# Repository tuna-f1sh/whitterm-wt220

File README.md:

```bash
        __        _______    ____  ____   ___
        \ \      / /_   _|  |___ \|___ \ / _ \
         \ \ /\ / /  | |_____ __) | __) | | | |
          \ V  V /   | |_____/ __/ / __/| |_| |
           \_/\_/    |_|    |_____|_____|\___/
       --- JBR Engineering Research Ltd 2019 ---
```

Design files, firmware and linux scripts for my _clever_ serial terminal, the
Whitterm-220 - WT-220. 

The WT-220 is a homage to the VT-220, providing a physical RS232 terminal with
the full features of a Linux computer running on a Raspberry Pi.

## Raspberry Pi Hat (./whitterm-hat)

KiCad design files for the rear io-panel:

* USB-C input for USB-PD high current (3 A) supply to RPi. LEDs indicate
  detected current profile from UFP. I2C lines made available to SAMD for
  playing with USB-C device modes.
* MAX3232 RS232 transceiver provides RS232 level interface to RPi UART and SAMD
  UART.
* SAMD21 microcontroller provides boot button control of RPi over I2C and
  buffered IO. Can be programmed over USB-C CDC-serial device or ISP.
* Control of RPi power supply from SAMD. Off by default allows safe start up, only when power input suitable/ready.
* DIP switch control of device UART connections (SAMD, RPi, RS232).
* Board replaces laser cut acrylic back piece from original design - it is
  both electronically and mechanically integrated.
* Lots of status LEDs 😃.

**There where a few green wires required for the first production (1.0). I
rolled these changes into the schematic but not fully updated the PCB.**

## Firmware (./firmware)

Arduino compatible firmware for rear panel SAMD21. Acts as I2C slave and
controls supply to RPi via 'Boot' button:

### Simplified State Diagram

```mermaid
graph TB;
    OFF-->|boot pressed 500 ms|ON;
    ON-->|I2C booted cmd recieved|BOOTED;
    ON-->|I2C recieve booted timeout 20000 ms|I2C_TIMEOUT;
    BOOTED-->|I2C recieve booted timeout 20000 ms|I2C_TIMEOUT;
    BOOTED-->|boot pressed 3000 ms|SHUTDOWN_REQUESTED;
    I2C_TIMEOUT-->|boot pressed 3000 ms|SHUTDOWN;
    I2C_TIMEOUT-->|I2C booted cmd recieved|BOOTED;
    SHUTDOWN_REQUESTED-->|I2C shutdown cmd|SHUTDOWN;
    SHUTDOWN_REQUESTED-->|boot pressed|ON;
    SHUTDOWN-->OFF;
```

## RPi Files (./rpi)

I started from a base Raspbian Lite image rather than Arch for this build.
Raspbian Lite is nice because I could install only what I wanted/needed. I
opted for I3WM since it's a keyboard terminal.

### Services

* boot: Runs shell script that displays boot ascii logo.
* i2c: Runs python I2C script (wt220-i2c.py) that configures case LEDs to act
  on RX/TX and then maintains link with I2C link with SAMD. Polls shutdown
  request state and acts on request by issuing system shutdown.
* poweroff: Runs on 'shutdown.target' and issues the final I2C shutdown
  command so that SAMD disables RPi 5 V.

### Config Files

Would make an install script for this if I was making more...

* xinitrc -> /etc/X11/xinit/xinitrc
* config.txt, cmdline.txt -> /boot/
* Xresources -> ~/.Xresources
* motd -> /etc/motd
* wt220-sshbanner.net -> /etc/wt220-sshbanner.net `Banner /etc/wt220-sshbanner.net` in
  /etc/ssh/sshd_config
* \*services. -> /lib/systemd/system/
* scripts -> /opt/wt220/

### Packages

Need to manually install
[`cool-retro-term`](https://github.com/Swordfish90/cool-retro-term)

Other packages in 'rpi/dpkg-selections.txt'

## Breakout (./whitterm-breakout)

DB9 GPIO breakout from V 1.0 rear panel

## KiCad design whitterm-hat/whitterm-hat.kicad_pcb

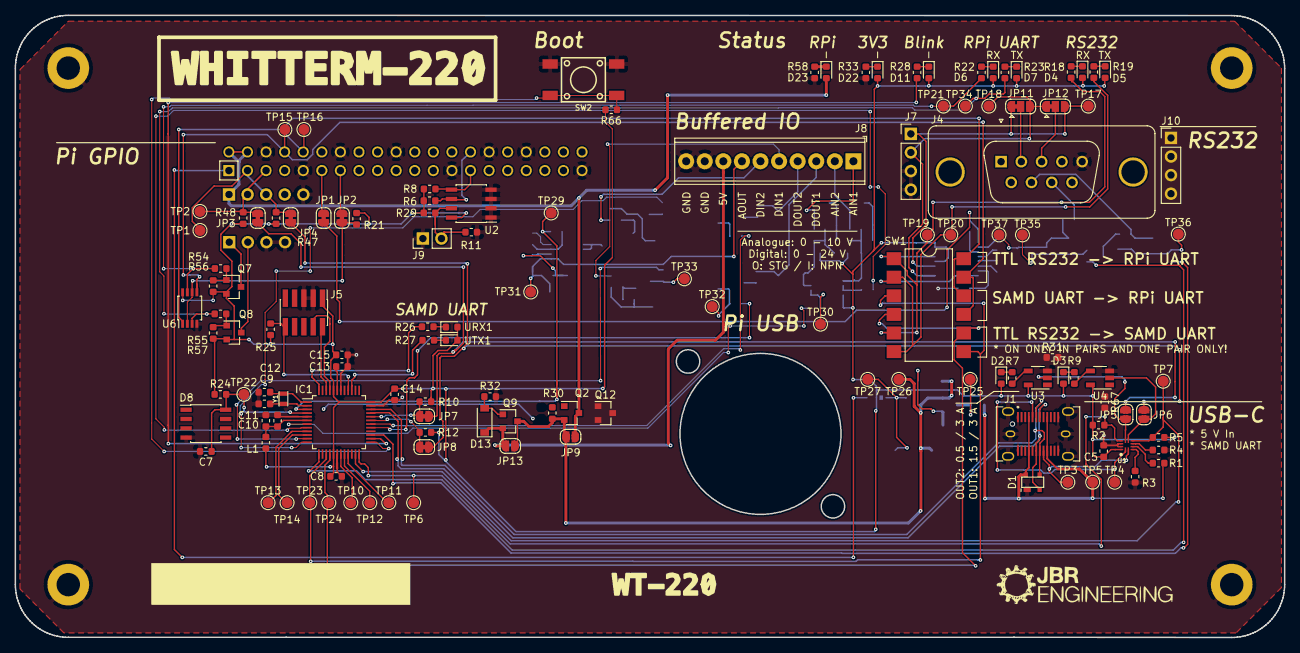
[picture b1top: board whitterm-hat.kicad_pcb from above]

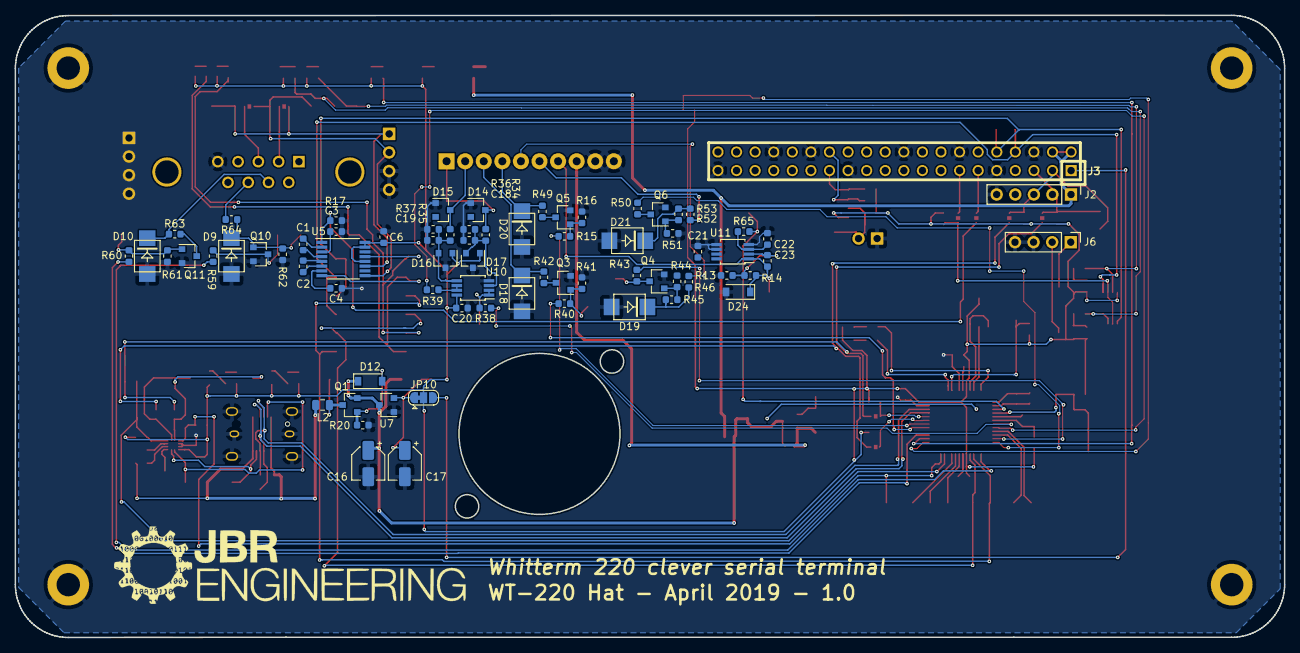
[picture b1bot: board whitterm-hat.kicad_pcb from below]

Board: 2 copper layers, 173.5 x 85.0 mm, 202 parts (72 on the bottom side), 127 nets.

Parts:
C1: 47nF; C_0603_1608Metric
C2, C3, C4: 330nF; C_0603_1608Metric
C5, C6, C18, C19, C20, C21: 100nF; C_0603_1608Metric
C7: 1uF; C_0603_1608Metric
C8, C10, C13, C14, C15: 0.1uF; C_0603_1608Metric
C9, C12: 15pF; C_0603_1608Metric
C11: 0.01uF; C_0603_1608Metric
C16, C17: 10uF; CP_Elec_4x5.3
C22: 470pF; C_0603_1608Metric
C23: 10pF; C_0603_1608Metric
D1: PRTR5V0U2X; SOT143B
D2: OUT2; LED_0603_1608Metric
D3: OUT1; LED_0603_1608Metric
D4: TLRX; LED_0603_1608Metric
D5: TLTX; LED_0603_1608Metric
D6: RXD; LED_0603_1608Metric
D7: TXD; LED_0603_1608Metric
D8: LM285D-2.5G; SOIC-8_3.9x4.9mm_P1.27mm
D9, D10, D18, D19, D20, D21: SMAJ30A-TR; D_DO-214AA
D11: D13; LED_0603_1608Metric
D12, D13: MMSZ16T1G; D_SOD-123
D14, D15: BZX84C10LT1G; D_SOT-23_ANK
D16, D17: BAV99; SOT-23
D22, D23: KP-2012MGC; LED_0603_1608Metric
D24: SMAJ12A-TR; D_SOD-123
IC1: SAMD21G18A; TQFP-48_7x7mm_P0.5mm
J1: USB_C_Receptacle; USB_C_Receptacle_JAE_DX07S024WJ1R350
J2: Touch I2C; PinHeader_1x05_P2.54mm_Vertical
J3: 40HAT; HEADER-2x20-REVERSE
J4: DB9_Male; DSUB-9_Male_Vertical_P2.77x2.84mm_MountingHoles
J5: Conn_02x05_Odd_Even; PinHeader_2x05_P1.27mm_Vertical_SMD
J6, J7, J10: Conn_01x04_Female; PinHeader_1x04_P2.54mm_Vertical
J8: Conn_01x10_Female; TerminalBlock_Phoenix_MPT-0,5-10-2.54_1x10_P2.54mm_Horizont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
J9: CONN_01X02; PinHeader_1x02_P2.54mm_Vertical
JP1, JP2, JP3, JP4, JP7, JP8: Jumper_2_Bridged; SolderJumper-2_P1.3mm_Bridged_RoundedPad1.0x1.5mm
JP5, JP6, JP9, JP13: Jumper_NO_Small; SolderJumper-2_P1.3mm_Open_RoundedPad1.0x1.5mm
JP10, JP11, JP12: SolderJumper_3_Bridged12; SolderJumper-3_P1.3mm_Bridged12_RoundedPad1.0x1.5mm
L1: LM18P; L_0603_1608Metric
L2: Ferrite_Bead_Small; L_0805_2012Metric
Q1, Q2, Q7, Q8, Q9: IRLML6402PBF; SOT-23
Q3, Q4, Q5, Q6, Q10, Q11, Q12: BC850; SOT-23
R1: 900k; R_0603_1608Metric
R2, R5, R17, R20, R21, R24, R25, R30, R31, R32, R56, R57, R66, R67: 10k; R_0603_1608Metric
R3, R4: 0R; R_0603_1608Metric
R6, R8, R10, R12, R47, R48: 4.7K; R_0603_1608Metric
R7, R9, R18, R19, R22, R23, R26, R27, R28, R33: 150R; R_0603_1608Metric
R11: DNP; R_0603_1608Metric
R13, R14: 100k; R_0603_1608Metric
R15, R40, R42, R43, R45, R46, R49, R50, R52, R53, R54, R55, R59, R60, R63, R64: 470R; R_0603_1608Metric
R16, R38, R39, R41, R44, R51, R61, R62, R65: 1k; R_0603_1608Metric
R29: 10K; R_0603_1608Metric
R34, R35: 9k1; R_0603_1608Metric
R36, R37: 3k9; R_0603_1608Metric
R58: 220R; R_0603_1608Metric
SW1: SW_DIP_x06; SMDIP-12_W9.53mm
SW2: SW_Push; SPST-4-PIN_6mm_sm
TP1, TP2, TP3, TP4, TP5, TP6, TP7, TP10, TP11, TP12, TP13, TP14, TP15, TP16, TP17, TP18, TP19, TP20, TP21, TP22, TP23, TP24, TP25, TP26, TP27, TP29, TP30, TP31, TP32, TP33, TP34, TP35, TP36, TP37: TestPoint; TestPoint_Pad_D1.5mm
U1: TUSB320; TI_RWB_X2QFN-12
U2: CAT24C32WI-GT3; SOIC-8_3.9x4.9mm_P1.27mm
U3, U4: 74LVC1G17; TSOT-23-5
U5: MAX3221; TSSOP-16_4.4x5mm_P0.65mm
U6: 74LVC2G02; TSSOP-8_3x3mm_P0.65mm
U7: MCP1703A-3302_SOT23; SOT-23
U10, U11: ADA4807-2ARM; MSOP-8_3x3mm_P0.65mm
URX1: RXD; LED_0603_1608Metric
UTX1: TXD; LED_0603_1608Metric
Y1: 32.768; Crystal_2-SMD_2x1.2mm
svg2mod: G***; whitterm220-fullname
svg2mod#2: G***; whitterm220-wt220

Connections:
+5V: C16.1, C21.2, D12.1, JP9.1, JP13.1, Q1.2, Q2.2, Q9.3, R30.1, TP26.1, U7.3, U11.8
/D+: D1.3, IC1.34, J1.A6, J1.B6
/D-: D1.2, IC1.33, J1.A7, J1.B7
/EXT_5VO: D13.1, J8.8, JP13.2, Q9.2
/ID_SC_EEPROM: J3.28, R6.1, U2.6
/ID_SD_EEPROM: J3.27, R8.1, U2.5
/PI_3V3: J3.1, JP10.3
/PI_5V: D23.2, J2.1, J3.2, J3.4, JP9.2, Q2.3
/PI_EN: IC1.14, Q12.1
/PI_RXD: J3.10, J10.1, SW1.10, SW1.12, TP16.1, U6.1
/PI_SCL: J2.2, J3.5, JP3.1, R48.1, TP2.1
/PI_SDA: J2.3, J3.3, JP4.1, R47.1, TP1.1
/PI_TXD: J3.8, J10.2, SW1.9, SW1.11, TP15.1, U6.5
/RS232-UART/RS232_CTS: J4.8, R64.2
/RS232-UART/RS232_RTS: D10.1, J4.7, R63.1
/RS232-UART/RS232_RX: J7.1, JP11.1, JP12.3, TP17.1, U5.11
/RS232-UART/RS232_TX: J7.2, JP11.3, JP12.1, TP18.1, U5.9
/RS232-UART/RXD_LEDC: J6.1, Q7.3
/RS232-UART/TTL_RX: R18.1, SW1.1, SW1.5, TP19.1, U5.13
/RS232-UART/TTL_TX: R19.1, SW1.2, SW1.6, TP20.1, U5.8
/RS232-UART/TXD_LEDC: J6.2, Q8.3
/SAMD_RXD: IC1.16, J10.3, SW1.4, SW1.8, TP24.1
/SAMD_TXD: IC1.15, J10.4, SW1.3, SW1.7, TP23.1
/USBC_ID: IC1.24, R2.1, TP6.1, U1.9
/USBC_INT: IC1.23, R5.1, TP7.1, U1.6
/USBC_SCL: JP3.2, JP5.2, JP7.1
/USBC_SDA: JP4.2, JP6.2, JP8.1
/U_CTS: IC1.13, R59.1
/U_RTS: IC1.27, R60.2
/buffers/AIN_I1: D14.1, J8.1, R34.2
/buffers/AIN_I2: D15.1, J8.2, R35.2
/buffers/AOUT_O1: C23.1, D24.1, J8.7, R14.1, TP31.1, U11.1
/buffers/DIN_I1: J8.5, R46.2
/buffers/DIN_I2: J8.6, R53.2
/buffers/DOUT_O1: D18.1, J8.3, R42.1
/buffers/DOUT_O2: D20.1, J8.4, R49.1
/microcontroller/A0_DAC: IC1.3, R65.2, TP29.1
/microcontroller/A1: IC1.7, R38.1
/microcontroller/A2: IC1.8, R39.1
/microcontroller/A3: IC1.9, TP13.1
/microcontroller/A4: IC1.10, TP14.1
/microcontroller/D6: IC1.29, R40.2
/microcontroller/D7: IC1.30, R15.2
/microcontroller/D8: IC1.11, R43.1
/microcontroller/D9: IC1.12, R50.1
/microcontroller/D11: IC1.25, R66.2, SW2.2
/microcontroller/D13: IC1.26, R28.1
/microcontroller/MISO: IC1.21, TP11.1
/microcontroller/MOSI: IC1.19, TP10.1
/microcontroller/NRST: IC1.40, J5.10, R25.2
/microcontroller/RX_LED: IC1.48, R26.1
/microcontroller/SCK: IC1.20, TP12.1
/microcontroller/SCL: IC1.32, JP7.2, R10.1
/microcontroller/SDA: IC1.31, JP8.2, R12.1
/microcontroller/SWDCLK: IC1.45, J5.4
/microcontroller/SWDIO: IC1.46, J5.2
/microcontroller/TX_LED: IC1.39, R27.1
/~RPI_EN_ACT: JP2.1, R21.1, U6.2, U6.6
/~RS232_EN: JP1.1, R17.2, U5.1
GND: C3.1, C4.1, C5.1, C6.1, C7.2, C8.2, C9.2, C10.2, C11.2, C12.2, C13.2, C14.2, C15.2, C16.2, C17.2, C18.2, C19.2, C20.1, C21.1, C22.2, D1.1, D8.4, D9.2, D10.2, D14.2, D15.2, D16.3, D17.3, D18.2, D19.2, D20.2, D21.2, D24.2, IC1.5, IC1.18, IC1.35, IC1.42, J1.A1, J1.A12, J1.B1, J1.B12, J1.S1, J2.5, J3.6, J3.9, J3.14, J3.20, J3.25, J3.30, J3.34, J3.39, J4.5, J5.3, J5.5, J6.3, J6.4, J7.3, J7.4, J8.9, J8.10, J9.1, Q3.2, Q4.2, Q5.2, Q6.2, Q10.2, Q11.2, Q12.2, R3.1, R4.1, R11.2, R13.1, R16.1, R17.1, R20.2, R32.2, R33.2, R36.1, R37.1, R41.1, R44.1, R51.1, R58.2, R61.1, R62.1, SW2.1, U1.10, U1.11, U2.1, U2.2, U2.3, U2.4, U3.3, U4.3, U5.14, U6.4, U7.1, U10.4, U11.4, U11.5, U11.6
unnamed: C1.1, U5.2
unnamed: C1.2, U5.4
unnamed: C2.1, U5.5
unnamed: C2.2, U5.6
unnamed: C3.2, U5.3
unnamed: C4.2, U5.7
unnamed: C7.1, D8.8, IC1.4, R24.2, TP22.1
unnamed: C9.1, IC1.2, Y1.1
unnamed: C10.1, C11.1, IC1.6, L1.1
unnamed: C12.1, IC1.1, Y1.2
unnamed: C13.1, IC1.43
unnamed: C17.1, JP10.1, TP27.1, U7.2
unnamed: C18.1, D17.2, R34.1, R36.2, U10.3
unnamed: C19.1, D16.2, R35.1, R37.2, U10.5
unnamed: C22.1, R65.1, U11.3
unnamed: C23.2, R13.2, R14.2, U11.2
unnamed: D2.1, R7.2
unnamed: D3.1, R9.2
unnamed: D4.1, R18.2
unnamed: D5.1, R19.2
unnamed: D6.1, R22.2
unnamed: D7.1, R23.1
unnamed: D9.1, Q10.1, R62.2, R64.1, TP37.1
unnamed: D11.1, R28.2
unnamed: D12.2, Q1.1, R20.1
unnamed: D13.2, Q9.1, R32.1
unnamed: D19.1, R45.2, R46.1
unnamed: D21.1, R52.2, R53.1
unnamed: D22.1, R33.1
unnamed: D23.1, R58.1
unnamed: J1.A5, TP4.1, U1.1
unnamed: J1.B5, TP3.1, U1.2
unnamed: J3.11, JP1.2
unnamed: J3.13, JP2.2
unnamed: J4.2, JP11.2
unnamed: J4.3, JP12.2
unnamed: J9.2, R11.1, R29.1, U2.7
unnamed: JP5.1, R31.1, U1.8, U3.2
unnamed: JP6.1, R67.1, U1.7, U4.2
unnamed: L2.1, Q1.3, TP25.1
unnamed: Q3.1, R40.1, R41.2, TP32.1
unnamed: Q3.3, R42.2
unnamed: Q4.1, R44.2, R45.1
unnamed: Q4.3, R43.2, TP33.1
unnamed: Q5.1, R15.1, R16.2
unnamed: Q5.3, R49.2
unnamed: Q6.1, R51.2, R52.1
unnamed: Q6.3, R50.2
unnamed: Q7.1, R54.2, R56.1
unnamed: Q8.1, R55.2, R57.1
unnamed: Q10.3, R59.2, TP35.1
unnamed: Q11.1, R60.1, R61.2, TP36.1
unnamed: Q11.3, R63.2
unnamed: Q2.1, Q12.3, R30.2
unnamed: R1.1, U1.4
unnamed: R3.2, U1.3
unnamed: R4.2, U1.5
unnamed: R7.1, U3.4
unnamed: R9.1, U4.4
unnamed: R22.1, R54.1, TP21.1, U6.7
unnamed: R23.2, R55.1, TP34.1, U6.3
unnamed: R26.2, URX1.1
unnamed: R27.2, UTX1.1
unnamed: R38.2, TP30.1, U10.1, U10.2
unnamed: R39.2, U10.6, U10.7
VBUS: D1.4, J1.A4, J1.A9, J1.B4, J1.B9, L2.2, R1.2, TP5.1
VCC: C5.2, C6.2, C8.1, C14.1, C15.1, C20.2, D2.2, D3.2, D4.2, D5.2, D6.2, D7.2, D11.2, D16.1, D17.1, D22.2, IC1.17, IC1.36, IC1.44, J5.1, JP10.2, L1.2, Q7.2, Q8.2, R2.2, R5.2, R6.2, R8.2, R10.2, R12.2, R21.2, R24.1, R25.1, R29.2, R31.2, R47.2, R48.2, R56.2, R57.2, R66.1, R67.2, U1.12, U2.8, U3.5, U4.5, U5.12, U5.15, U5.16, U6.8, U10.8, URX1.2, UTX1.2

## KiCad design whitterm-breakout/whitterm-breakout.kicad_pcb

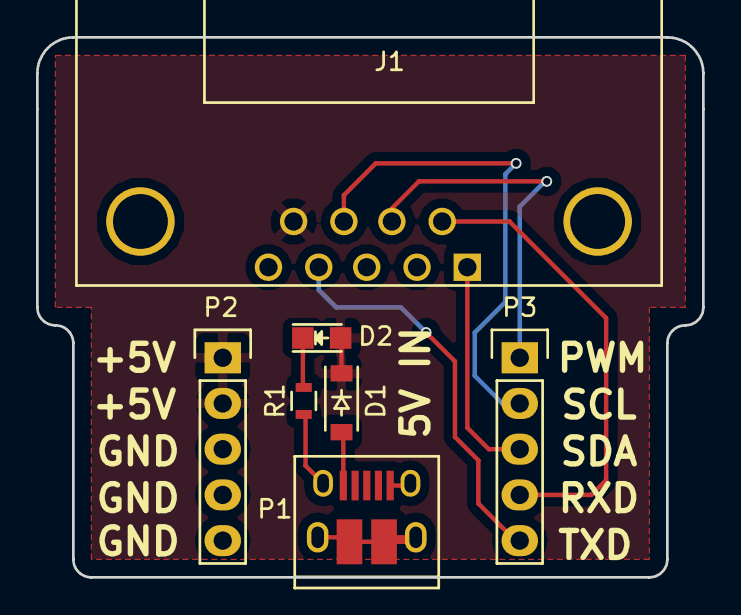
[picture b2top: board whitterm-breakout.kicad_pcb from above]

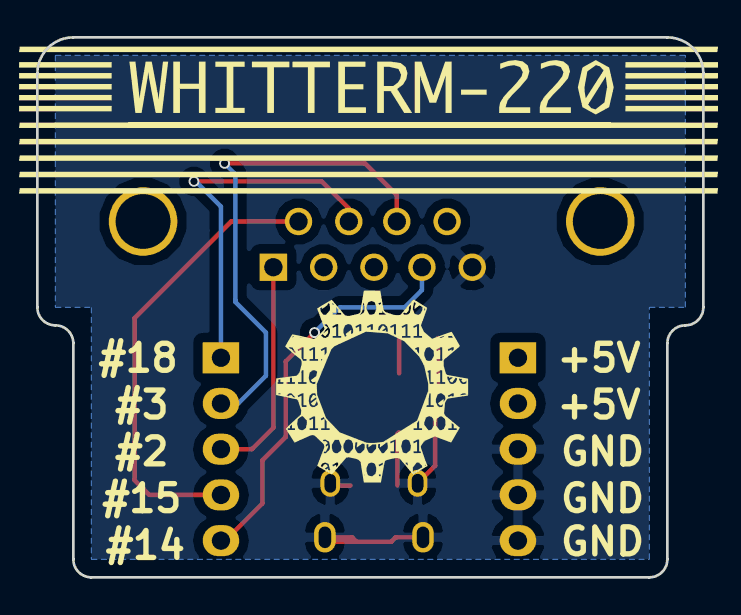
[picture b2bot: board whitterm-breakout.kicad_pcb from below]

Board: 2 copper layers, 37.0 x 30.0 mm, 9 parts (2 on the bottom side), 9 nets.

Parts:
D1: MBR0520L; SOD-123
D2: LED; LED_0805
J1: DB9; DB9MC
P1: USB_OTG; USB_Micro-B_10103594-0001LF
P2, P3: CONN_01X05; Pin_Header_Straight_1x05
R1: R330; R_0603
jbrbinary: G***; jbrbinary
whitterm220-logo: G***; whitterm220

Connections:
#2_SDA: J1.1, P3.3
#3_SCL: J1.8, P3.2
#14_TXD: J1.4, P3.5
#15_RXD: J1.6, P3.4
#18_PWM: J1.7, P3.1
GND: J1.5, P1.5, P1.6, P2.3, P2.4, P2.5, R1.2
unnamed: D1.2, P1.1
unnamed: D2.1, R1.1
VCC: D1.1, D2.2, J1.9, P2.1, P2.2

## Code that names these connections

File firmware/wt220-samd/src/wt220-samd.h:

#ifndef WT220_SAMD_H
#define WT220_SAMD_H

// internal defines
#define VERSION_MAJOR         0
#define VERSION_MINOR         1

#define DEBUG                 false
#define DEBUG_DEVICE          1 // 0 USB, 1 Uart (ExtSerial)
#define ECHO_EXTSERIAL        true

#define PRINT_AIN             false
#define PRINT_GRAPH           false

// hardware pins
#define LED_PIN               13

#define BOOT_BTN_PIN          11
#define NOT_PI_EN_PIN         3

#define RS232_CTS_PIN         4
#define RS232_RTS_PIN         10

#define USBC_INT_PIN          2
#define USBC_ID_PIN           5

#define AIN1_PIN              A1
#define AIN2_PIN              A2
#define DOUT1_PIN             6
#define DOUT2_PIN             7
#define DIN1_PIN              8
#define DIN2_PIN              9
#define AOUT1_PIN             DAC0

// buffers
#define USE_EXT_REF           false
#if USE_EXT_REF
#define EXT_ALOG_REF          2.501 // measured with meter
#else
#define EXT_ALOG_REF          3.300
#endif
#define ALOG_RESOLUTION_BITS  12
#define DAC_RESOLUTION_BITS   12 // is it actually 10 bits but Arduino function maps value passed to alog resolution bits :o
#define MAX_ALOG_VALUE        ((1 << ALOG_RESOLUTION_BITS) - 1)
#define MAX_DAC_VALUE         ((1 << DAC_RESOLUTION_BITS) - 1)

#define AIN_GAIN              3.33
#define AIN_MAX_VOLTAGE       10.0
#define AOUT_GAIN             3
#define AOUT_MAX_VOLTAGE      3.30 // for PCB 1.0 due to Vcc supply to Op-amp

#define BOOT_HOLD_DELAY       500
#define SHUTDOWN_HOLD_DELAY   3000

// led states
enum class state_t {
  PI_OFF,
  PI_ON,
  PI_BOOTED,
  SHUTDOWN_REQUEST,
  SHUTTING_DOWN,
  I2C_TIMEOUT
};

void startShutdown(uint16_t timeout);
state_t getState(void);
void setState(state_t state);

#endif

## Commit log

2019-03-16 first commit, hat schematic captured
2019-04-05 pcb sent for production
2019-05-31 firmware added and bring up R value changes
2019-06-05 button button logic
2019-06-10 mods during bring up, see notes
2019-06-10 bring up firmware, all hardware testing and changes rolled into schematic
2019-06-12 titles in header file and some tidying
2019-06-14 stuff from rpi
2019-06-14 correct pin and logic for activity LED
2019-06-16 i2c monitor script and service
2019-06-16 firmware functionally complete for basic button usage
2019-06-18 fix power off service user
2019-06-18 remove abort shutdown so that hard shutdown available
2019-06-20 add i2c timeout state
2019-06-20 further bring up changes
2019-06-20 Create LICENSE
2019-06-20 README and eeprom files
2019-06-20 add render of mermaid state
2019-07-04 buffer on RS232 LEDs
2019-07-07 add gpl header
2019-09-25 add rescue lib for hat PCB
